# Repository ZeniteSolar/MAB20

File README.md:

# MAB20
**M**odulo de **A**cionamento das **B**ombas de porão

Embarcação Guarapuvu II

Equipe Zênite Solar

### Sobre

O módulo de acionamento das bombas encarrega-se de receber os dados que o piloto envia por meio
do Módulo de Interface de Controle (MIC), ou pelo sensor de altura da água, usando uma interface CAN, rede
que diminui o número de cabos no sistema e diminui seu peso.
Pela regra, o circuito das baterias auxiliares deve ser isolado da bateria principal, a rede CAN está
conectada no circuito da principal, para isolar os dados da rede são recebidos por um microcontrolador e
isolados com opto-acopladores.

#### Requisitos
1. Ligar as bombas de Porão
    - Ligar por controle manual
    - Ligar por controle automatico
2. Manter as baterias isoladas galvanicamente
     - Usar isolamento otico
3. Proteções
     - Limitar a corrente de transiente do relé para não queimar  o transistor de acionamento 
     - Fusiveis
     - Filtrar ruidos que possam resultar em falsos acionamentos

#### Abordagens
1.Driver da bomba

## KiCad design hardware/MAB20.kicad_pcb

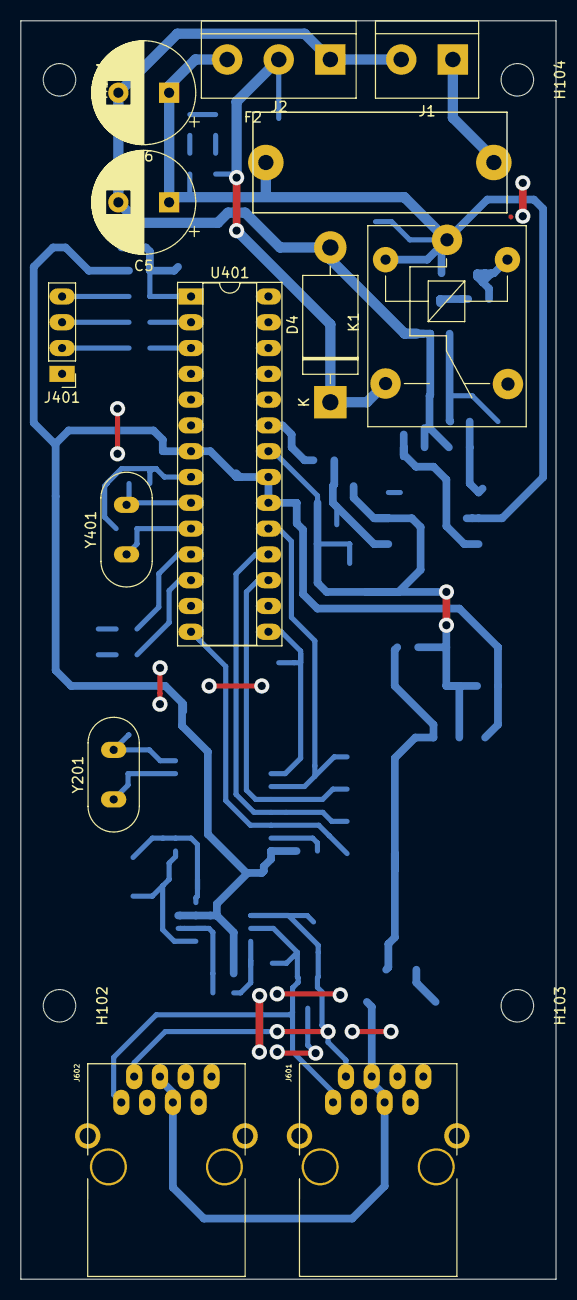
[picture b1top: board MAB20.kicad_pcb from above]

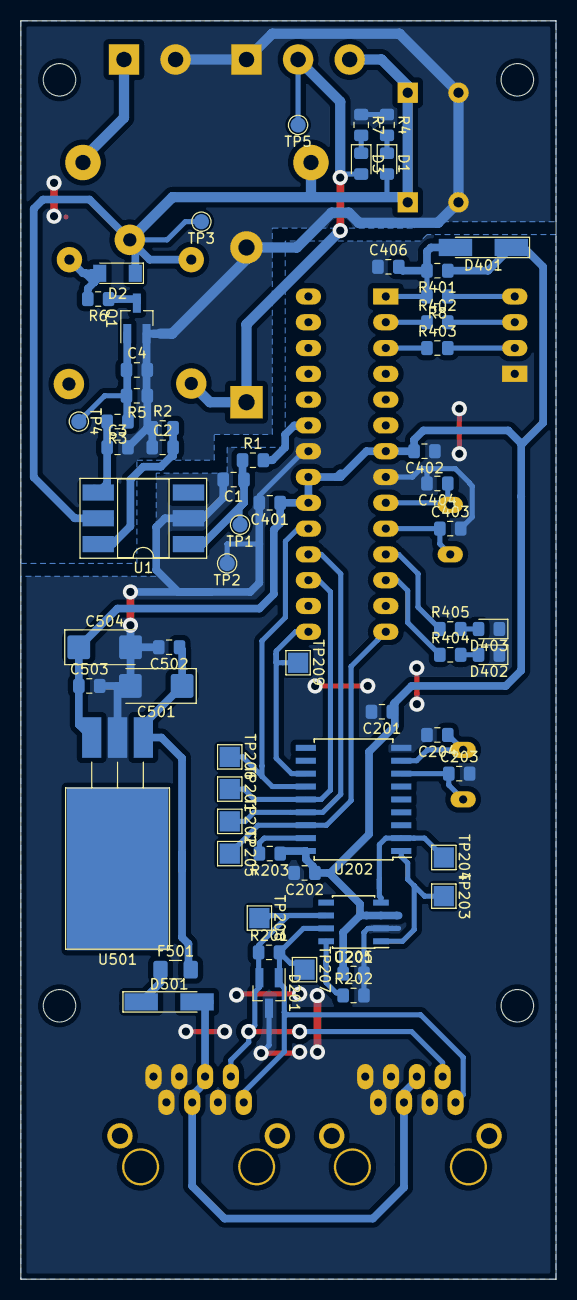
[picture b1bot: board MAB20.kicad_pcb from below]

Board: 2 copper layers, 52.7 x 123.9 mm, 79 parts (62 on the bottom side), 43 nets.

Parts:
C1, C3, C4: 100n; C_0805_2012Metric_Pad1.15x1.40mm_HandSolder
C2: 1n; C_0805_2012Metric_Pad1.15x1.40mm_HandSolder
C5, C6: 4700u 35V; CP_Radial_D10.0mm_P5.00mm
C201, C202, C205, C401, C402, C406, C502, C503: 100nF; C_0805_2012Metric_Pad1.15x1.40mm_HandSolder
C203, C204, C403, C404: 22pF; C_0805_2012Metric_Pad1.15x1.40mm_HandSolder
C501, C504: 1uF; CP_EIA-6032-20_AVX-F_Pad2.25x2.35mm_HandSolder
D1: G3mm; LED_0805_2012Metric_Pad1.15x1.40mm_HandSolder
D2: LL4148; D_MiniMELF
D3: R3mm; LED_0805_2012Metric_Pad1.15x1.40mm_HandSolder
D4: MUR460; D_DO-201AD_P15.24mm_Horizontal
D201: pesd1can; SOT-23_Handsoldering
D401, D501: LL4148; D_MiniMELF_Handsoldering
D402, D403: LED_RED; LED_0805_2012Metric_Pad1.15x1.40mm_HandSolder
F2: 10A; Fuse_Holder_5x20
F501: 500mA; Fuse_1206_3216Metric_Pad1.42x1.75mm_HandSolder
H101, H102, H103, H104: MountingHole; MountingHole_3.2mm_M3
J1: Screw_Terminal_01x02; TerminalBlock_bornier-2_P5.08mm
J2: Screw_Terminal_01x03; TerminalBlock_bornier-3_P5.08mm
J401: USART; PinHeader_1x04_P2.54mm_Vertical
J601, J602: RJ45; RJ45_YH59_01
K1: coil: 12VDC, contact: 125V/10A; Relay_SPDT_SANYOU_SRD_Series_Form_C
Q1: BCV27; SOT-23_Handsoldering
R1: 330R; R_0805_2012Metric_Pad1.15x1.40mm_HandSolder
R2: NC; R_0805_2012Metric_Pad1.15x1.40mm_HandSolder
R3: 1k2; R_0805_2012Metric_Pad1.15x1.40mm_HandSolder
R4, R7, R402, R403, R404, R405: 1k; R_0805_2012Metric_Pad1.15x1.40mm_HandSolder
R5, R203, R401: 10k; R_0805_2012Metric_Pad1.15x1.40mm_HandSolder
R6: 120R; R_0805_2012Metric_Pad1.15x1.40mm_HandSolder
R8: 100R; R_0805_2012Metric_Pad1.15x1.40mm_HandSolder
R201: 120; R_0805_2012Metric_Pad1.15x1.40mm_HandSolder
R202: 4k7; R_0805_2012Metric_Pad1.15x1.40mm_HandSolder
TP1: A1; TestPoint_Pad_D1.5mm
TP2: K1; TestPoint_Pad_D1.5mm
TP3: 12V; TestPoint_Pad_D1.5mm
TP4: B1; TestPoint_Pad_D1.5mm
TP5: OUT1; TestPoint_Pad_D1.5mm
TP201: SI; TestPoint_Pad_2.0x2.0mm
TP202: SO; TestPoint_Pad_2.0x2.0mm
TP203: TXCAN; TestPoint_Pad_2.0x2.0mm
TP204: RXCAN; TestPoint_Pad_2.0x2.0mm
TP205: SC; TestPoint_Pad_2.0x2.0mm
TP206: SCK; TestPoint_Pad_2.0x2.0mm
TP207: CAN_H; TestPoint_Pad_2.0x2.0mm
TP208: CAN_L; TestPoint_Pad_2.0x2.0mm
TP209: INT; TestPoint_Pad_2.0x2.0mm
U1: 4N25; DIP-6_W8.89mm_SMDSocket_LongPads
U201: MCP2551-I/SN; SOIC-8_3.9x4.9mm_P1.27mm
U202: MCP2515-xSO; SOIC-18W_7.5x11.6mm_P1.27mm
U401: ATMEGA328P-PU; DIP-28_W7.62mm_Socket
U501: LM7805; TO-220-3_Horizontal_TabDown_SMD
Y201, Y401: 16MHz; Crystal_HC49-U_Vertical

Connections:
+5V: C201.1, C202.1, C205.1, C401.1, C402.2, C503.1, C504.1, D401.1, R203.1, R401.1, U201.3, U202.18, U401.7, U401.20, U401.21, U501.3
+12V: C5.1, C6.1, D1.2, D2.1, F2.1, J2.3, K1.1, K1.2, TP3.1, U1.5
/CANBUS CONN/CAN_H: D201.1, J601.1, J602.1, R201.2, TP207.1, U201.7
/CANBUS CONN/CAN_L: D201.2, J601.2, J602.2, R201.1, TP208.1, U201.6
/CANBUS/CS: TP205.1, U202.16, U401.14
/CANBUS/INT: TP209.1, U202.12, U401.15
/CANBUS/RXCAN: TP204.1, U201.4, U202.2
/CANBUS/TXCAN: TP203.1, U201.1, U202.1
/MCU/LED1: R405.1, U401.11
/MCU/LED2: R404.1, U401.12
/MCU/ON_OFF_PUMP: R1.2, U401.23
/MCU/RESET: C406.2, D401.2, R8.2, R401.2, U401.1
/MCU/USART_RX: R402.1, U401.2
/MCU/USART_TX: R403.1, U401.3
/MISO: TP202.1, U202.15, U401.18
/MOSI: TP201.1, U202.14, U401.17
/POWER SUPPLY/+18V_IN: D501.2, J601.4, J601.5, J602.4, J602.5
/POWER SUPPLY/+18V_OUT: C501.1, C502.1, F501.2, U501.1
/SCK: TP206.1, U202.13, U401.19
/filter/Vin: F2.2, J1.1
/pump_driver/+Pump: D3.2, D4.1, J2.2, K1.3, TP5.1
GND: C1.2, C201.2, C202.2, C203.2, C204.2, C205.2, C401.2, C402.1, C403.2, C404.2, C406.1, C501.2, C502.2, C503.2, C504.2, D201.3, D402.1, D403.1, J401.1, J601.3, J601.6, J601.7, J601.8, J602.3, J602.6, J602.7, J602.8, R202.2, TP2.1, U1.2, U201.2, U202.9, U401.8, U401.22, U501.2
GNDPWR: C2.1, C3.2, C4.2, C5.2, C6.2, D4.2, J1.2, J2.1, Q1.2, R2.1, R4.1, R5.1, R7.1
unnamed: C1.1, R1.1, TP1.1, U1.1
unnamed: C2.2, R2.2, U1.6
unnamed: C3.1, R3.2, U1.4
unnamed: C4.1, Q1.1, R3.1, R5.2, TP4.1
unnamed: C203.1, U202.7, Y201.1
unnamed: C204.1, U202.8, Y201.2
unnamed: C403.1, U401.10, Y401.1
unnamed: C404.1, U401.9, Y401.2
unnamed: D1.1, R4.2
unnamed: D2.2, K1.5, R6.2
unnamed: D3.1, R7.2
unnamed: D402.2, R404.2
unnamed: D403.2, R405.2
unnamed: D501.1, F501.1
unnamed: J401.2, R403.2
unnamed: J401.3, R402.2
unnamed: J401.4, R8.1
unnamed: Q1.3, R6.1
unnamed: R202.1, U201.8
unnamed: R203.2, U202.17

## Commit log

2020-07-19 clone of MAB19 and gitignore
2020-07-20 layout
2020-07-20 size optimization
2020-07-20 more size optimizing
2020-07-20 minor updates
2020-08-01 img exports
2020-08-02 Revision: Clean in/out of sheets and power píns
2020-08-02 Fix some 3D components and add more space between connectors and the fuse holder
2020-09-03 Create LICENSE
2022-03-19 Add firmware gitignore.
2022-03-19 Remove binaries
2022-03-19 makefile: Add several compiler flags, change optimization to 's', use system installed avr-gcc.
2022-03-19 Use extern modifier to fix duplicated variables being defined on newer GCC
2022-03-19 Fix missing declarations.
